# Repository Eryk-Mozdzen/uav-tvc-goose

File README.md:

# Thrust Vector Control Single Rotor UAV ''Goose''

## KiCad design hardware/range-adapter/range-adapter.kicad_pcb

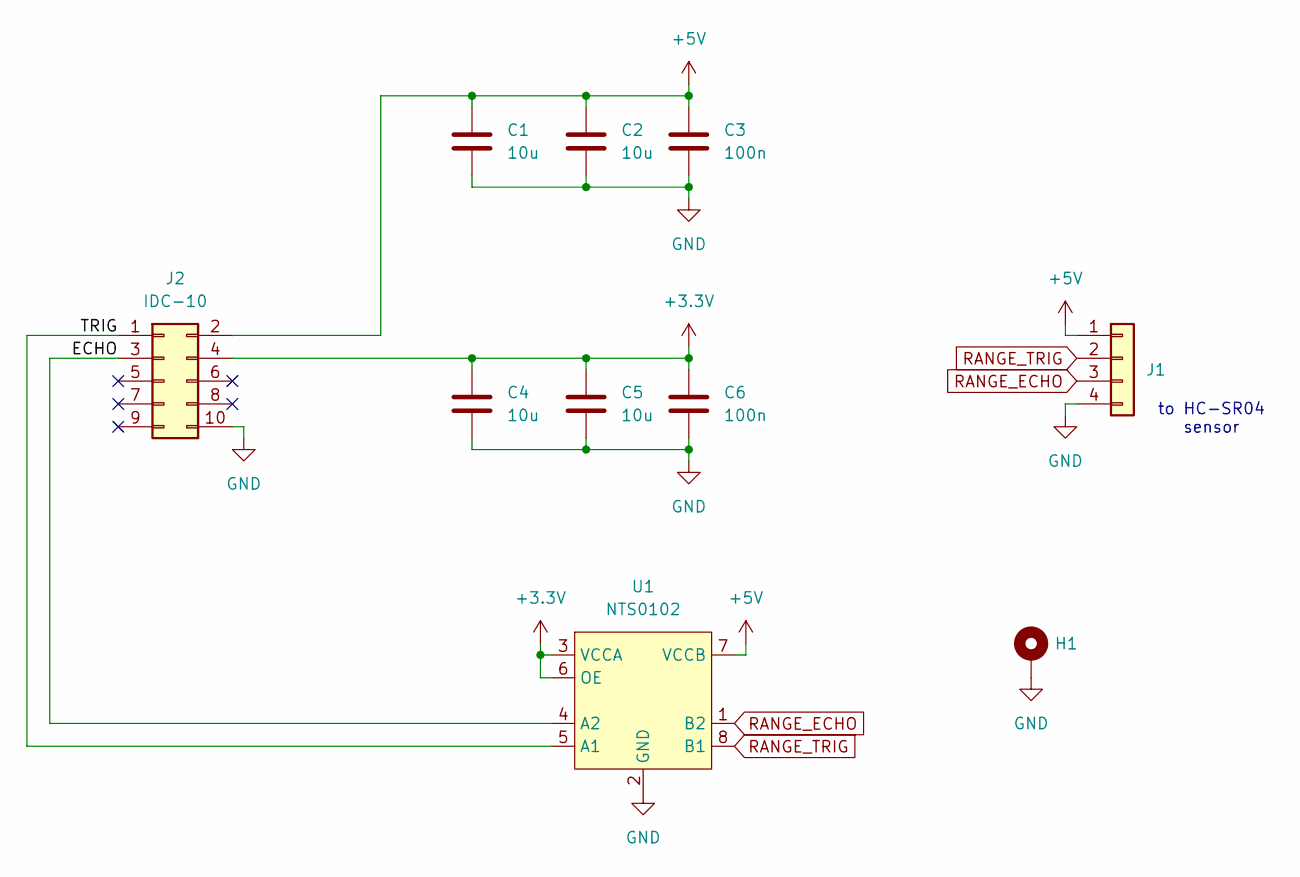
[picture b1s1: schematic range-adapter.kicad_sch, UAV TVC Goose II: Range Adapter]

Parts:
C1, C2, C4, C5: 10u; C_0603_1608Metric
C3, C6: 100n; C_0603_1608Metric
H1: MountingHole_Pad; MountingHole_3.5mm_Pad_Via
J1: Conn_01x04; header_1x4_not_used
J2: IDC-10; IDC-10-vertical
U1: NTS0102

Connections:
+3.3V: C4.1, C5.1, C6.1, J2.4, U1.3 (VCCA), U1.6 (OE)
+5V: C1.1, C2.1, C3.1, J1.1, J2.2, U1.7 (VCCB)
/ECHO: J2.3, U1.4 (A2)
/TRIG: J2.1, U1.5 (A1)
GND: C1.2, C2.2, C3.2, C4.2, C5.2, C6.2, H1.1, J1.4, J2.10, U1.2 (GND)
RANGE_ECHO: J1.3, U1.1 (B2)
RANGE_TRIG: J1.2, U1.8 (B1)

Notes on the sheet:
to HC-SR04 sensor

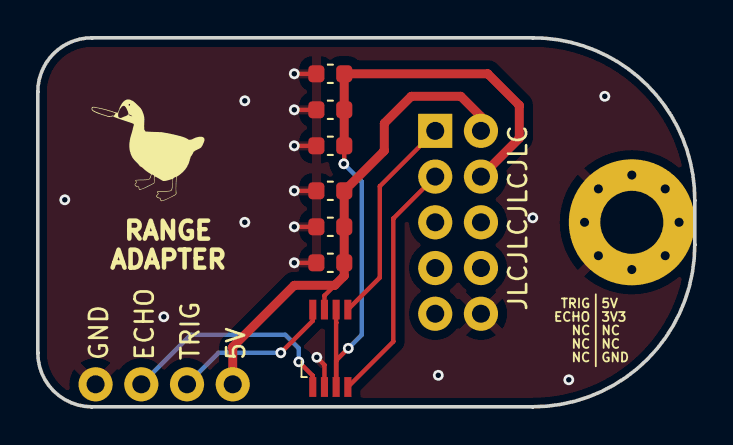
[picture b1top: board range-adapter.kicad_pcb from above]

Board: 2 copper layers, 36.5 x 20.5 mm, 10 parts (0 on the bottom side), 7 nets.

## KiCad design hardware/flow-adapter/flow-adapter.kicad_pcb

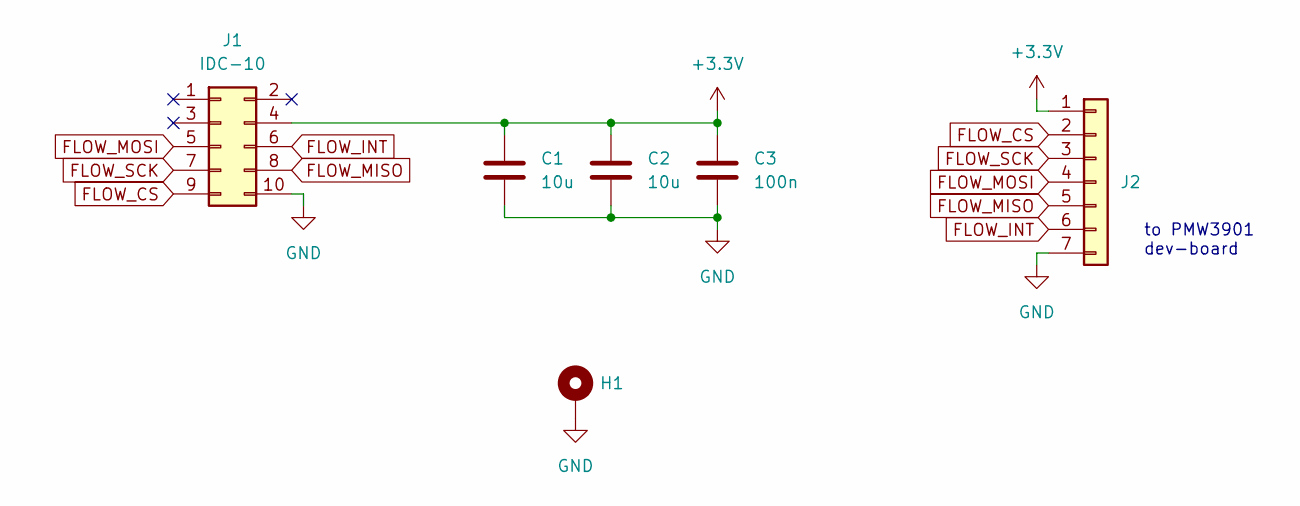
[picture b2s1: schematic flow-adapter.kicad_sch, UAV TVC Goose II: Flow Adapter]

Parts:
C1, C2: 10u; C_0603_1608Metric
C3: 100n; C_0603_1608Metric
H1: MountingHole_Pad; MountingHole_3.5mm_Pad_Via
J1: IDC-10; IDC-10-vertical
J2: Conn_01x07; header_1x7_not_used

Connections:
+3.3V: C1.1, C2.1, C3.1, J1.4, J2.1
FLOW_CS: J1.9, J2.2
FLOW_INT: J1.6, J2.6
FLOW_MISO: J1.8, J2.5
FLOW_MOSI: J1.5, J2.4
FLOW_SCK: J1.7, J2.3
GND: C1.2, C2.2, C3.2, H1.1, J1.10, J2.7

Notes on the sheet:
to PMW3901 dev-board

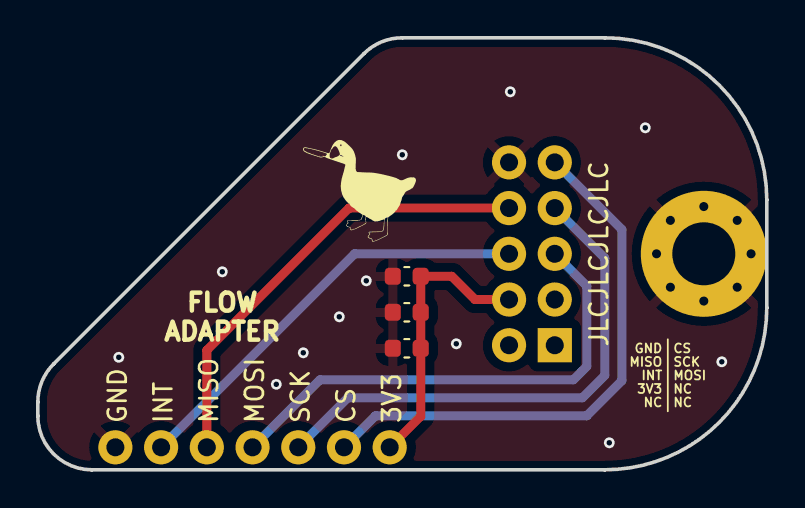
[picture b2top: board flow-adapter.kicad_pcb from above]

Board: 2 copper layers, 40.5 x 24.0 mm, 6 parts (0 on the bottom side), 7 nets.

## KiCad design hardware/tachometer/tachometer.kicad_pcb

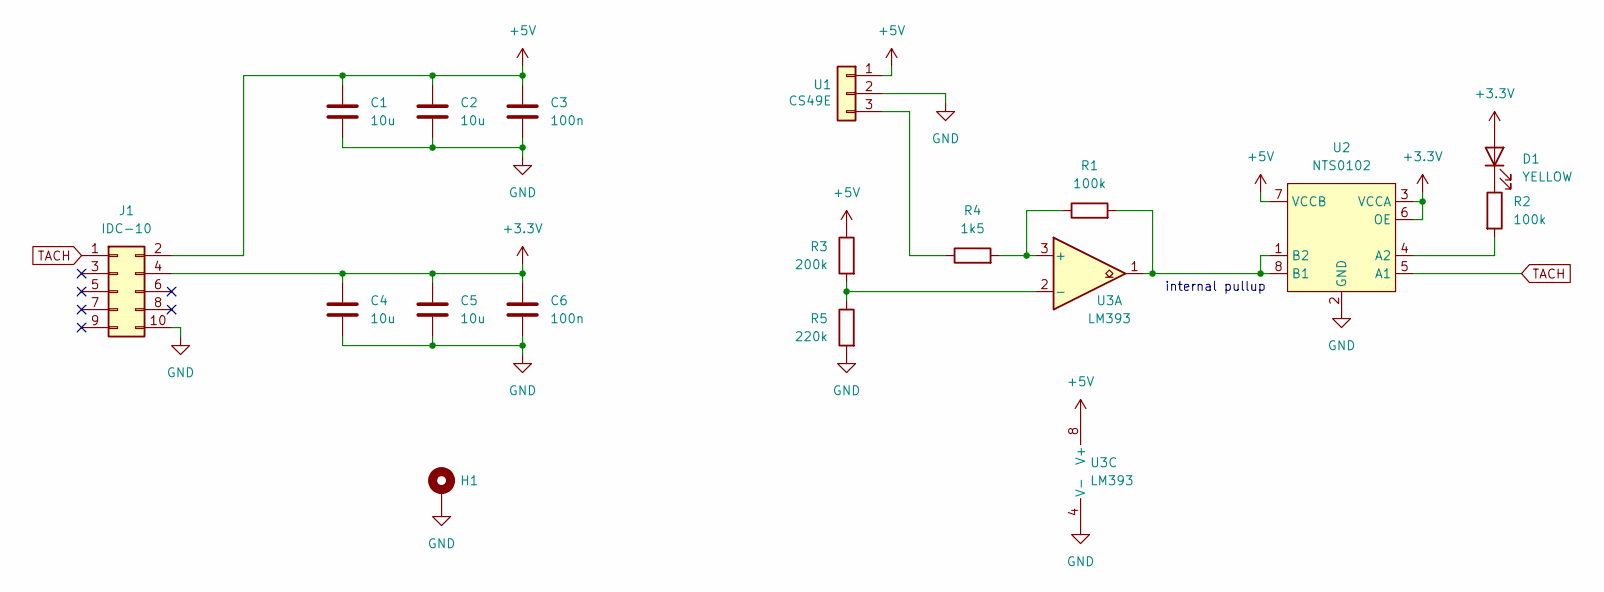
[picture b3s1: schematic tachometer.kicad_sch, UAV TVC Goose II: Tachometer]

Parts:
C1, C2, C4, C5: 10u; C_0603_1608Metric
C3, C6: 100n; C_0603_1608Metric
D1: YELLOW; LED_0603_1608Metric
H1: MountingHole_Pad; MountingHole_3.5mm_Pad_Via
J1: IDC-10; IDC-10-vertical
R1: 100k; R_0805_2012Metric
R2: 100k; R_0603_1608Metric
R3: 200k; R_0805_2012Metric
R4: 1k5; R_0805_2012Metric
R5: 220k; R_0805_2012Metric
U1: CS49E; hall
U2: NTS0102
U3: LM393

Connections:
+3.3V: C4.1, C5.1, C6.1, D1.2 (A), J1.4, U2.3 (VCCA), U2.6 (OE)
+5V: C1.1, C2.1, C3.1, J1.2, R3.1, U1.1, U2.7 (VCCB), U3.8 (V+)
GND: C1.2, C2.2, C3.2, C4.2, C5.2, C6.2, H1.1, J1.10, R5.2, U1.2, U2.2 (GND), U3.4 (V-)
unnamed: D1.1 (K), R2.1
unnamed: R4.1, U1.3
unnamed: R2.2, U2.4 (A2)
unnamed: R1.2, U2.1 (B2), U2.8 (B1), U3.1
unnamed: R1.1, R4.2, U3.3 (+)
unnamed: R3.2, R5.1, U3.2 (-)
TACH: J1.1, U2.5 (A1)

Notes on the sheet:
internal pullup

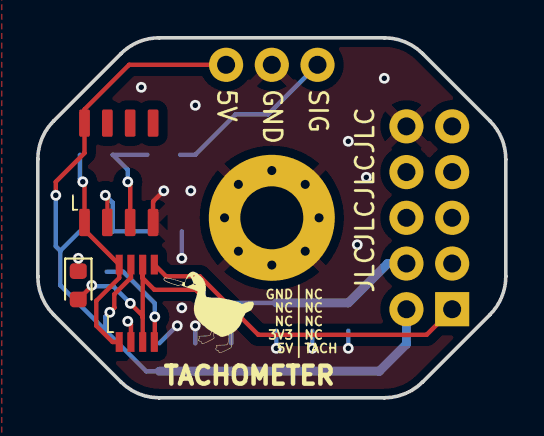
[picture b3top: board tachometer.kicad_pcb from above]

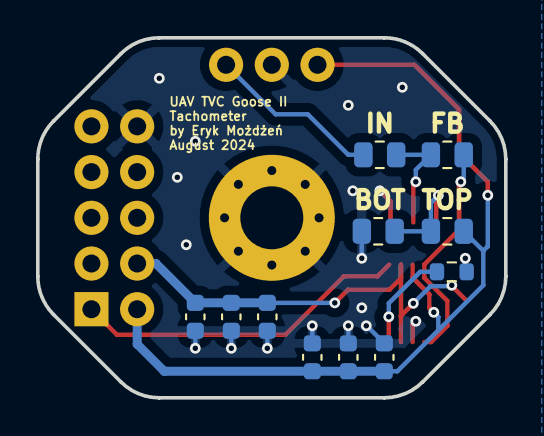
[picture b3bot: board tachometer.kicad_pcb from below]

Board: 2 copper layers, 26.0 x 20.0 mm, 17 parts (12 on the bottom side), 10 nets.

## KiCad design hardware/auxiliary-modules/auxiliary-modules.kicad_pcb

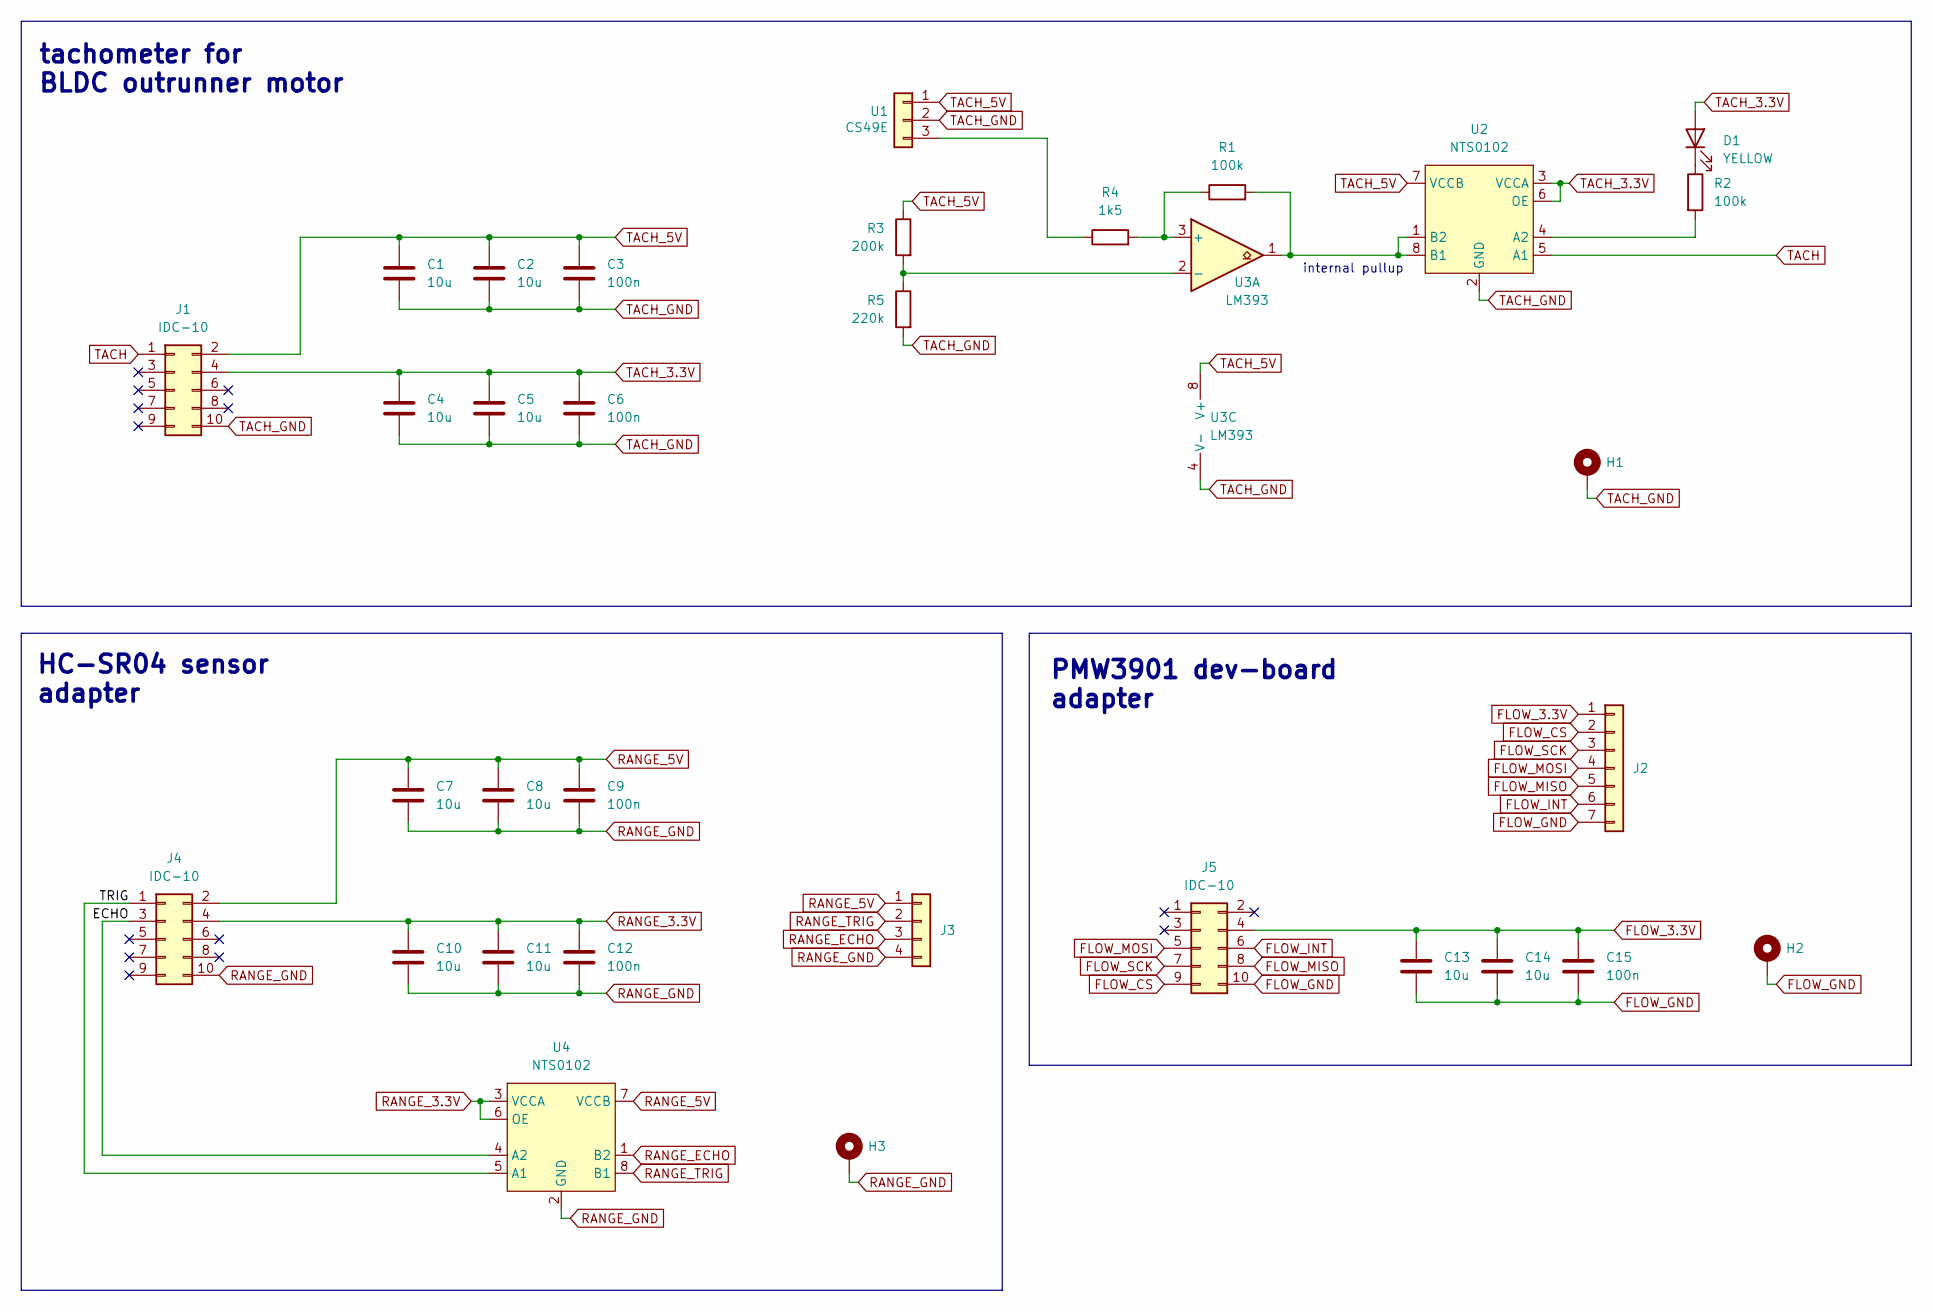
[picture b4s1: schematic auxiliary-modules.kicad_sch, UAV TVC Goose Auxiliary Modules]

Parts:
C1, C2, C4, C5, C7, C8, C10, C11, C13, C14: 10u; C_0603_1608Metric
C3, C6, C9, C12, C15: 100n; C_0603_1608Metric
D1: YELLOW; LED_0603_1608Metric
H1, H2, H3: MountingHole_Pad; MountingHole_3.5mm_Pad_Via
J1, J4, J5: IDC-10; IDC-10_vertical
J2: Conn_01x07; header_1x7
J3: Conn_01x04; header_1x4
R1: 100k; R_0805_2012Metric
R2: 100k; R_0603_1608Metric
R3: 200k; R_0805_2012Metric
R4: 1k5; R_0805_2012Metric
R5: 220k; R_0805_2012Metric
U1: CS49E; hall
U2, U4: NTS0102
U3: LM393

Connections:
/ECHO: J4.3, U4.4 (A2)
/TRIG: J4.1, U4.5 (A1)
FLOW_3.3V: C13.1, C14.1, C15.1, J2.1, J5.4
FLOW_CS: J2.2, J5.9
FLOW_GND: C13.2, C14.2, C15.2, H2.1, J2.7, J5.10
FLOW_INT: J2.6, J5.6
FLOW_MISO: J2.5, J5.8
FLOW_MOSI: J2.4, J5.5
FLOW_SCK: J2.3, J5.7
unnamed: D1.1 (K), R2.1
unnamed: R4.1, U1.3
unnamed: R2.2, U2.4 (A2)
unnamed: R1.2, U2.1 (B2), U2.8 (B1), U3.1
unnamed: R1.1, R4.2, U3.3 (+)
unnamed: R3.2, R5.1, U3.2 (-)
RANGE_3.3V: C10.1, C11.1, C12.1, J4.4, U4.3 (VCCA), U4.6 (OE)
RANGE_5V: C7.1, C8.1, C9.1, J3.1, J4.2, U4.7 (VCCB)
RANGE_ECHO: J3.3, U4.1 (B2)
RANGE_GND: C7.2, C8.2, C9.2, C10.2, C11.2, C12.2, H3.1, J3.4, J4.10, U4.2 (GND)
RANGE_TRIG: J3.2, U4.8 (B1)
TACH: J1.1, U2.5 (A1)
TACH_3.3V: C4.1, C5.1, C6.1, D1.2 (A), J1.4, U2.3 (VCCA), U2.6 (OE)
TACH_5V: C1.1, C2.1, C3.1, J1.2, R3.1, U1.1, U2.7 (VCCB), U3.8 (V+)
TACH_GND: C1.2, C2.2, C3.2, C4.2, C5.2, C6.2, H1.1, J1.10, R5.2, U1.2, U2.2 (GND), U3.4 (V-)

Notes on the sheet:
internal pullup
HC-SR04 sensor adapter
tachometer for BLDC outrunner motor
PMW3901 dev-board adapter

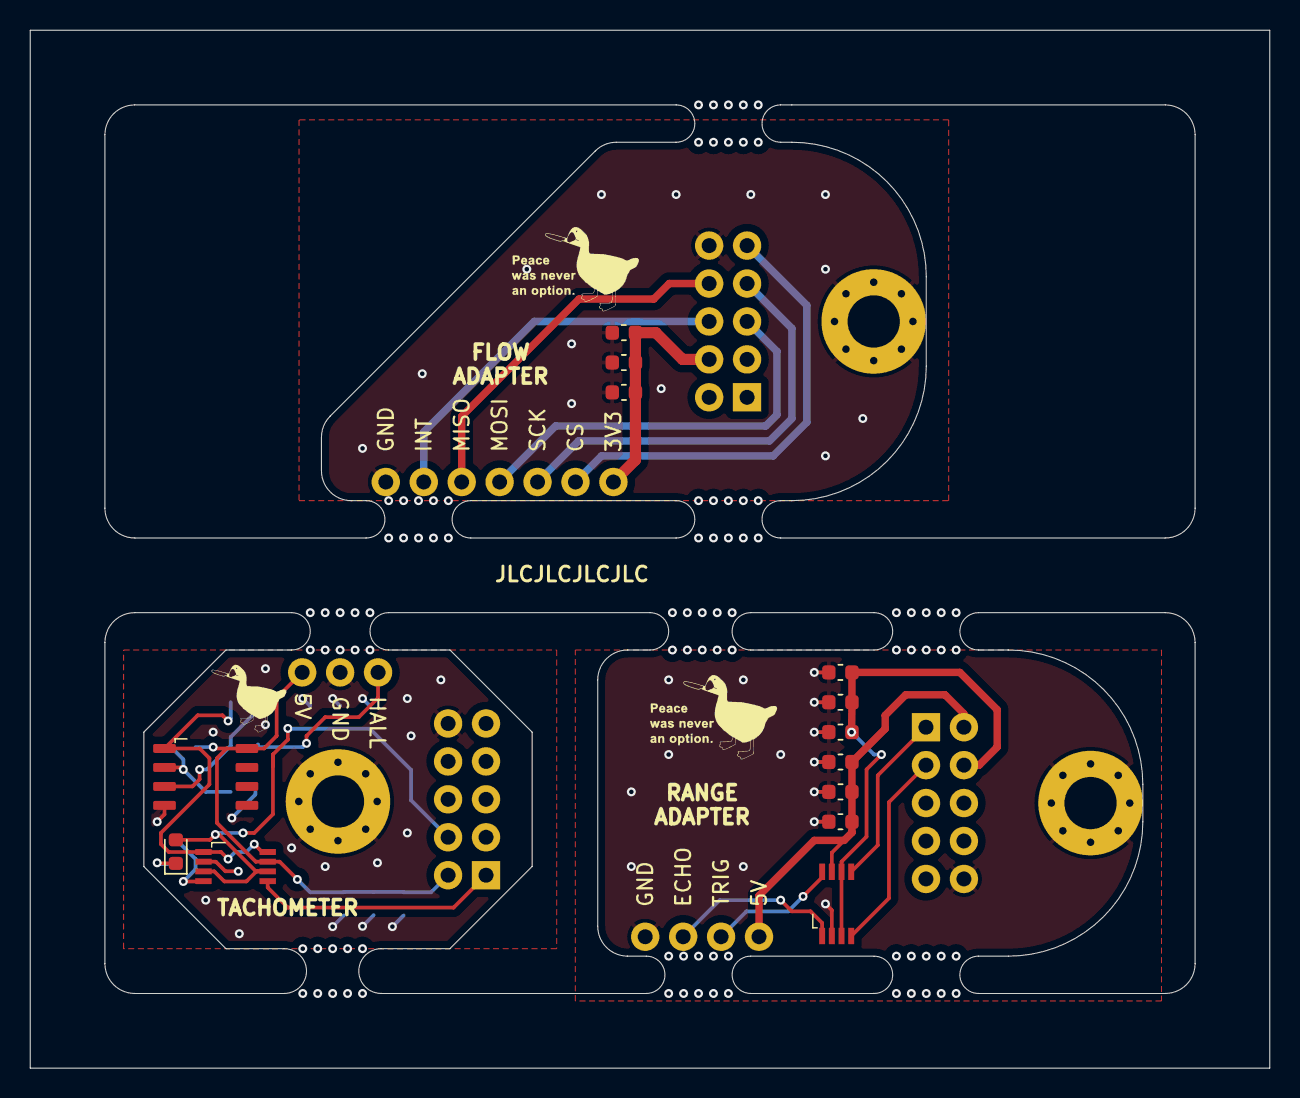
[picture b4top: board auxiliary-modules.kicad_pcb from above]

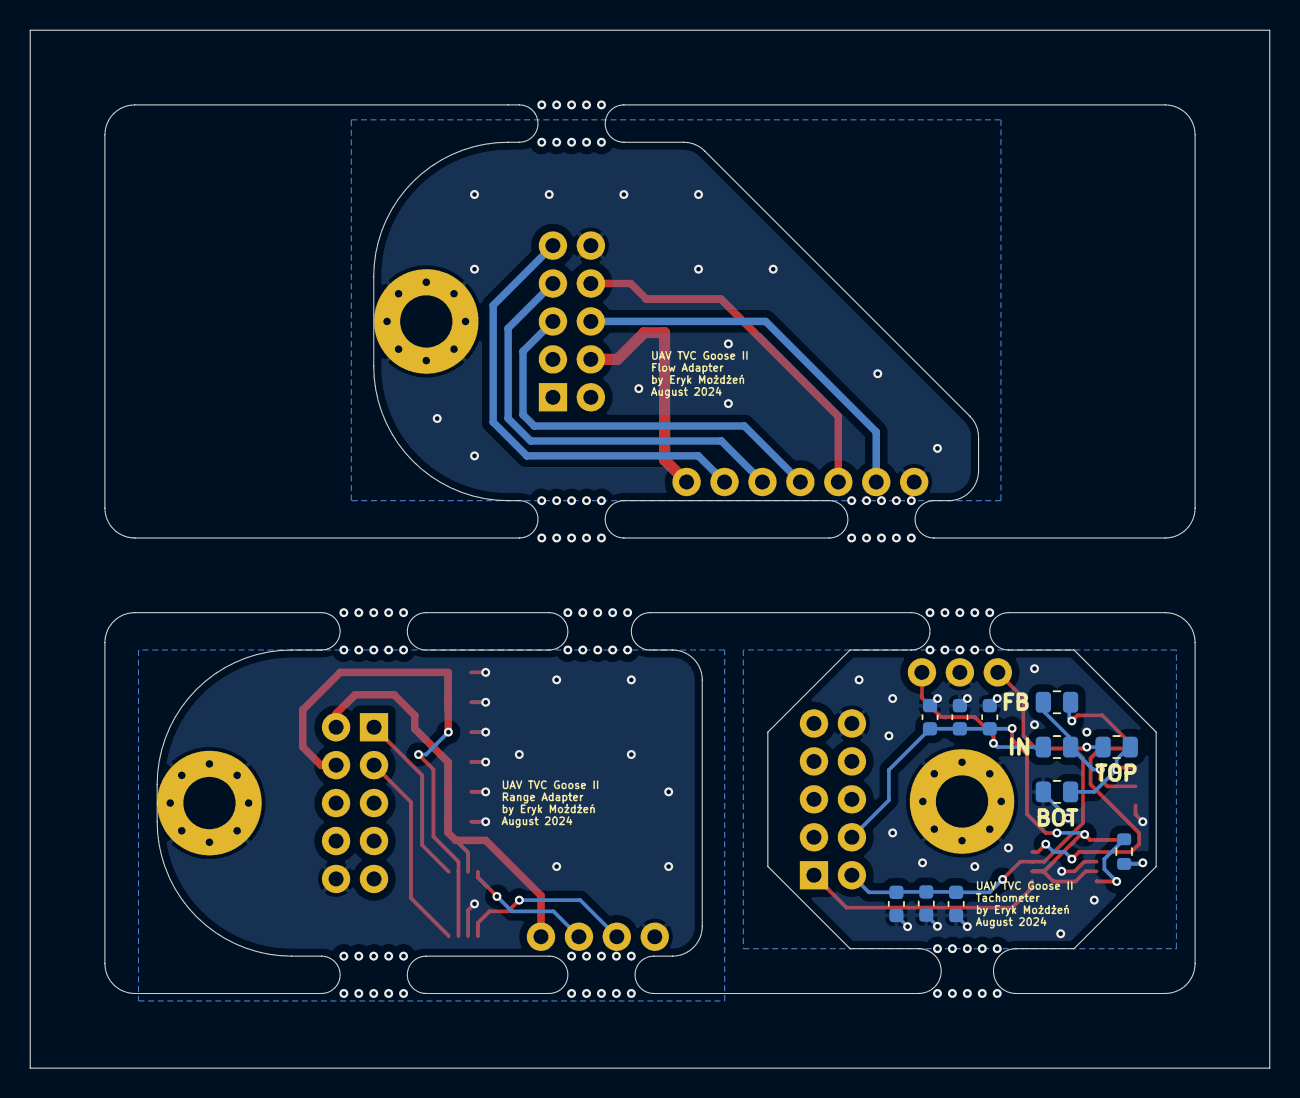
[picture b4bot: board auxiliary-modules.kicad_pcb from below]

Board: 2 copper layers, 83.0 x 69.5 mm, 33 parts (12 on the bottom side), 24 nets.

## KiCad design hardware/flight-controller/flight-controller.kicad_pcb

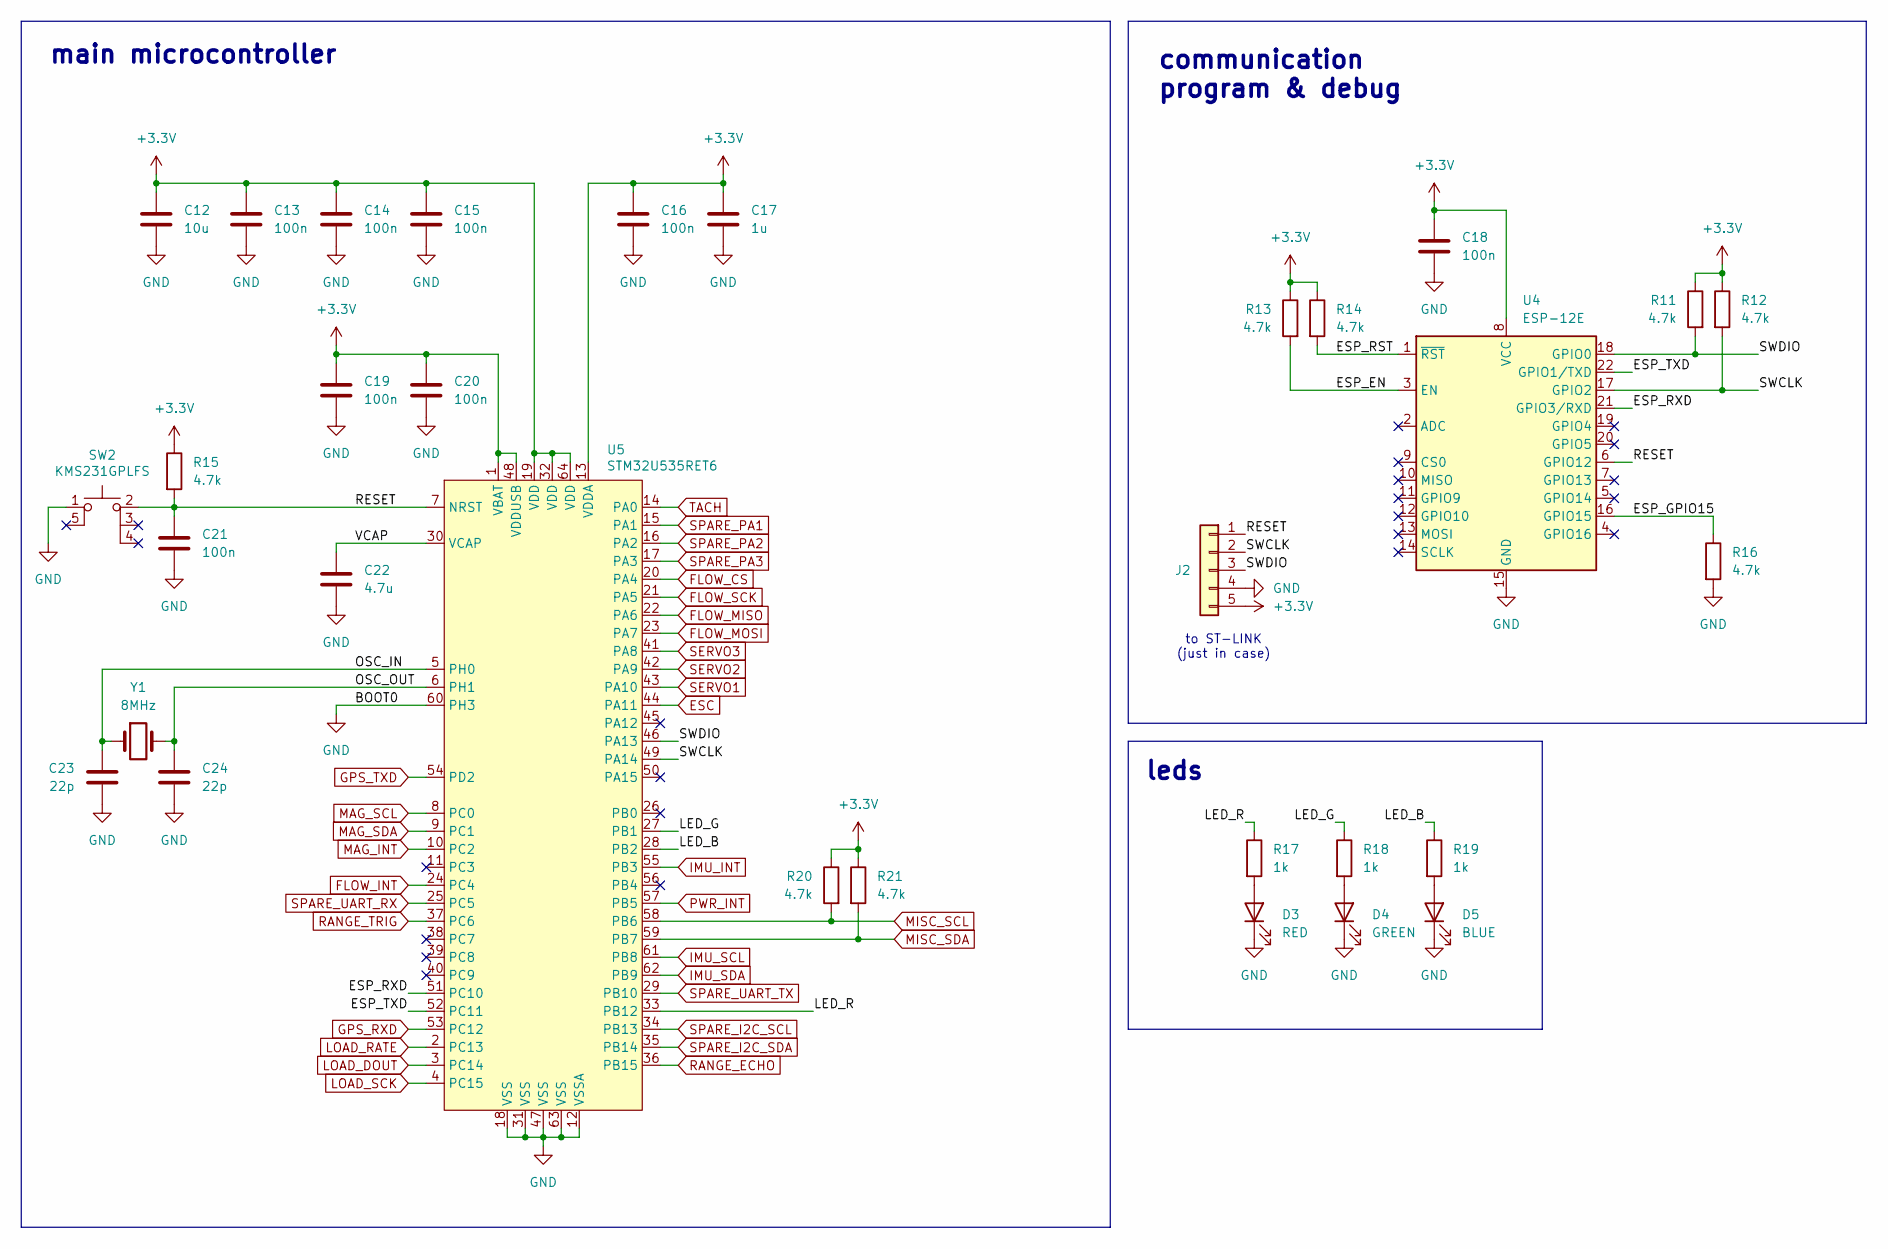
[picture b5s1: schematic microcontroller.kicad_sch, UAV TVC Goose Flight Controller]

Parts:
C12: 10u; C_0603_1608Metric
C13, C14, C15, C16, C18, C19, C20, C21: 100n; C_0603_1608Metric
C17: 1u; C_0603_1608Metric
C22: 4.7u; C_0603_1608Metric
C23, C24: 22p; C_0603_1608Metric
D3: RED; LED_0603_1608Metric
D4: GREEN; LED_0603_1608Metric
D5: BLUE; LED_0603_1608Metric
J2: Conn_01x05; header_1x5_not_used
R11, R12, R13, R14, R15, R16, R20, R21: 4.7k; R_0603_1608Metric
R17, R18, R19: 1k; R_0603_1608Metric
SW2: KMS231GPLFS
U4: ESP-12E
U5: STM32U535RET6
Y1: 8MHz; oscillator_5032_2

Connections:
+3.3V: C12.1, C13.1, C14.1, C15.1, C16.1, C17.1, C18.1, C19.1, C20.1, J2.5, R11.1, R12.1, R13.1, R14.1, R15.1, R20.1, R21.1, U4.8 (VCC), U5.1 (VBAT), U5.13 (VDDA), U5.19 (VDD), U5.32 (VDD), U5.48 (VDDUSB), U5.64 (VDD); also elsewhere on the board
/microcontroller/ESP_EN: R13.2, U4.3 (EN)
/microcontroller/ESP_GPIO15: R16.1, U4.16 (GPIO15)
/microcontroller/ESP_RST: R14.2, U4.1 (~RST)
/microcontroller/ESP_RXD: U4.21 (GPIO3/RXD), U5.51 (PC10)
/microcontroller/ESP_TXD: U4.22 (GPIO1/TXD), U5.52 (PC11)
/microcontroller/LED_B: R19.1, U5.28 (PB2)
/microcontroller/LED_G: R18.1, U5.27 (PB1)
/microcontroller/LED_R: R17.1, U5.33 (PB12)
/microcontroller/OSC_IN: C23.1, U5.5 (PH0), Y1.1
/microcontroller/OSC_OUT: C24.1, U5.6 (PH1), Y1.2
/microcontroller/RESET: C21.1, J2.1, R15.2, SW2.2, U4.6 (GPIO12), U5.7 (NRST)
/microcontroller/SWCLK: J2.2, R12.2, U4.17 (GPIO2), U5.49 (PA14)
/microcontroller/SWDIO: J2.3, R11.2, U4.18 (GPIO0), U5.46 (PA13)
/microcontroller/VCAP: C22.1, U5.30 (VCAP)
ESC: U5.44 (PA11); also elsewhere on the board
FLOW_CS: U5.20 (PA4); also elsewhere on the board
FLOW_INT: U5.24 (PC4); also elsewhere on the board
FLOW_MISO: U5.22 (PA6); also elsewhere on the board
FLOW_MOSI: U5.23 (PA7); also elsewhere on the board
FLOW_SCK: U5.21 (PA5); also elsewhere on the board
GND: C12.2, C13.2, C14.2, C15.2, C16.2, C17.2, C18.2, C19.2, C20.2, C21.2, C22.2, C23.2, C24.2, D3.1 (K), D4.1 (K), D5.1 (K), J2.4, R16.2, SW2.1, U4.15 (GND), U5.12 (VSSA), U5.18 (VSS), U5.31 (VSS), U5.47 (VSS), U5.60 (PH3), U5.63 (VSS); also elsewhere on the board
GPS_RXD: U5.53 (PC12); also elsewhere on the board
GPS_TXD: U5.54 (PD2); also elsewhere on the board
IMU_INT: U5.55 (PB3); also elsewhere on the board
IMU_SCL: U5.61 (PB8); also elsewhere on the board
IMU_SDA: U5.62 (PB9); also elsewhere on the board
LOAD_DOUT: U5.3 (PC14); also elsewhere on the board
LOAD_RATE: U5.2 (PC13); also elsewhere on the board
LOAD_SCK: U5.4 (PC15); also elsewhere on the board
MAG_INT: U5.10 (PC2); also elsewhere on the board
MAG_SCL: U5.8 (PC0); also elsewhere on the board
MAG_SDA: U5.9 (PC1); also elsewhere on the board
MISC_SCL: R20.2, U5.58 (PB6); also elsewhere on the board
MISC_SDA: R21.2, U5.59 (PB7); also elsewhere on the board
unnamed: D3.2 (A), R17.2
unnamed: D4.2 (A), R18.2
unnamed: D5.2 (A), R19.2
PWR_INT: U5.57 (PB5); also elsewhere on the board
RANGE_ECHO: U5.36 (PB15); also elsewhere on the board
RANGE_TRIG: U5.37 (PC6); also elsewhere on the board
SERVO1: U5.43 (PA10); also elsewhere on the board
SERVO2: U5.42 (PA9); also elsewhere on the board
SERVO3: U5.41 (PA8); also elsewhere on the board
SPARE_I2C_SCL: U5.34 (PB13); also elsewhere on the board
SPARE_I2C_SDA: U5.35 (PB14); also elsewhere on the board
SPARE_PA1: U5.15 (PA1); also elsewhere on the board
SPARE_PA2: U5.16 (PA2); also elsewhere on the board
SPARE_PA3: U5.17 (PA3); also elsewhere on the board
SPARE_UART_RX: U5.25 (PC5); also elsewhere on the board
SPARE_UART_TX: U5.29 (PB10); also elsewhere on the board
TACH: U5.14 (PA0); also elsewhere on the board

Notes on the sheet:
main microcontroller
to ST-LINK (just in case)
communication program & debug
leds

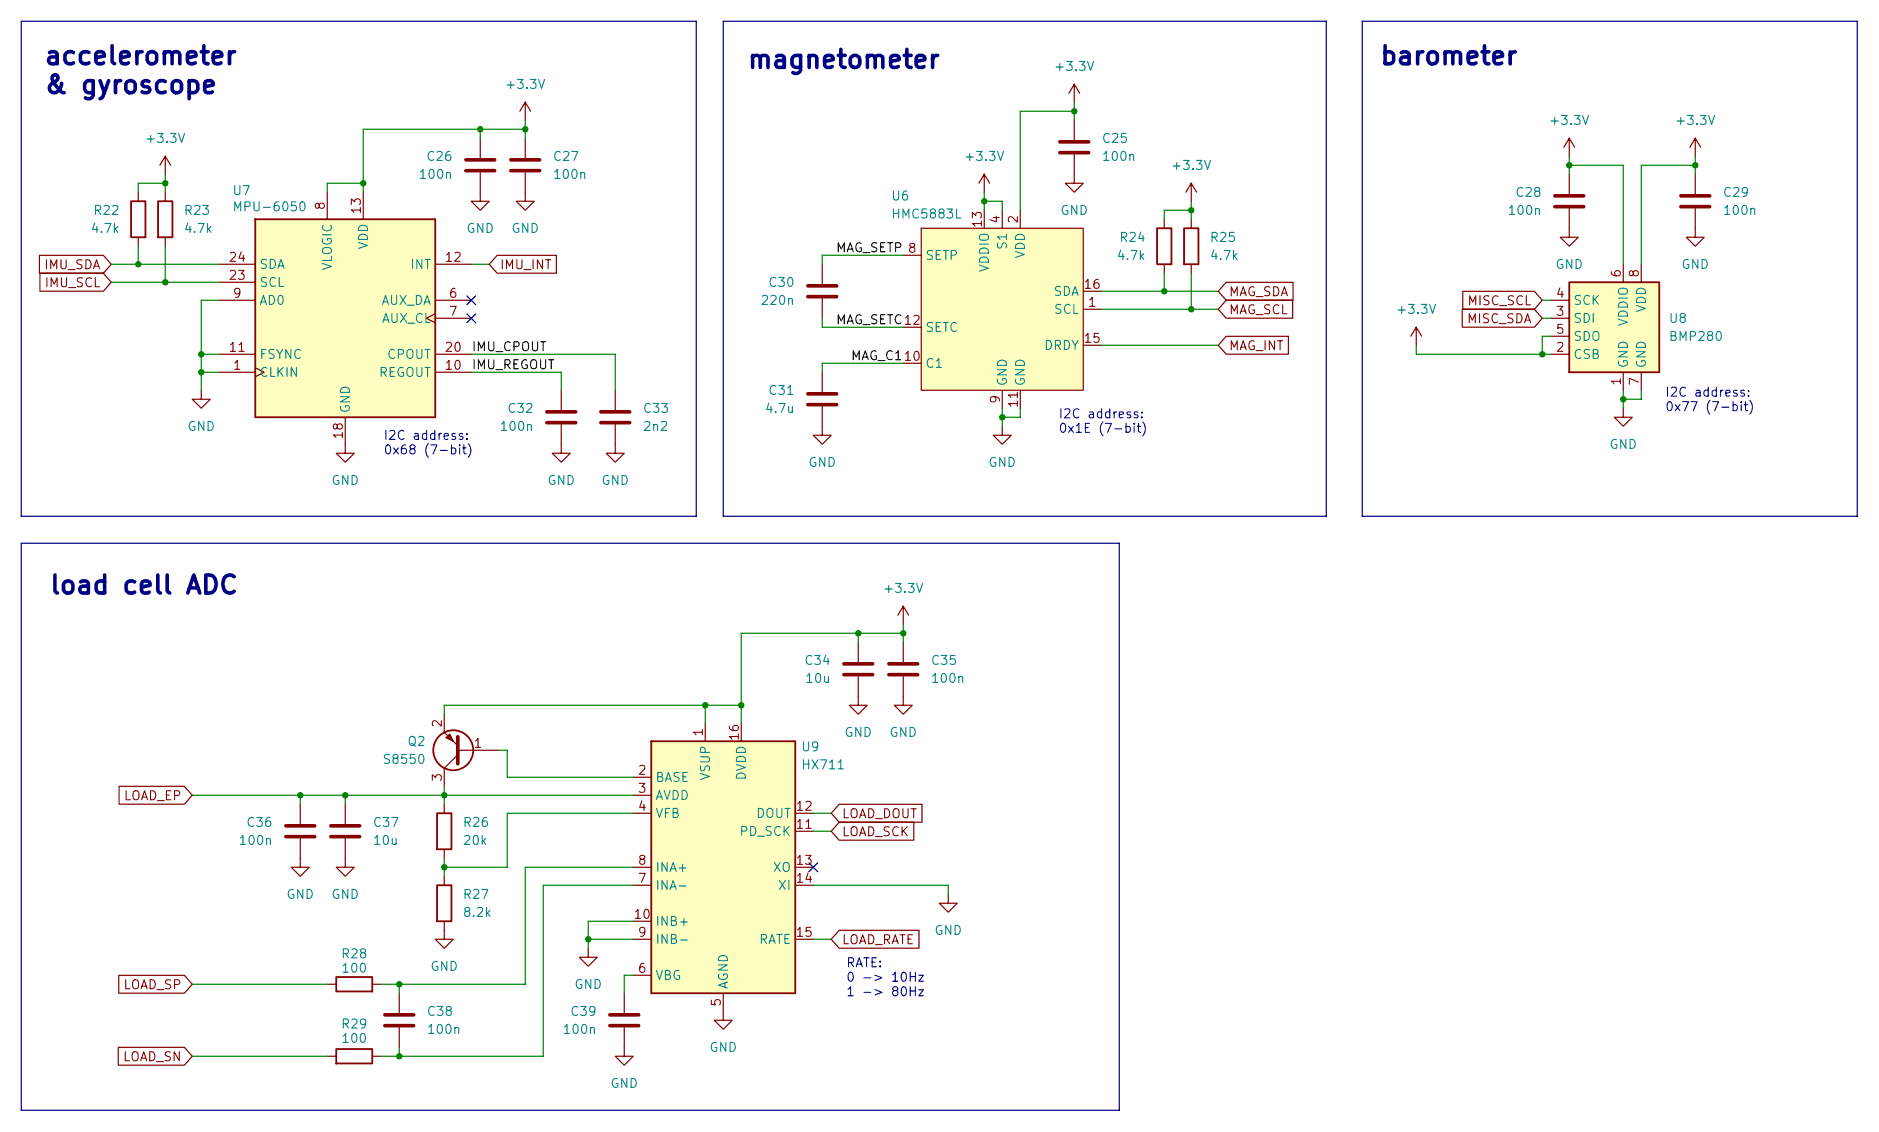
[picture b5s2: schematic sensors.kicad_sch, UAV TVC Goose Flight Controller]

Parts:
C25, C26, C27, C28, C29, C32, C35, C36, C38, C39: 100n; C_0603_1608Metric
C30: 220n; C_0603_1608Metric
C31: 4.7u; C_0603_1608Metric
C33: 2n2; C_0603_1608Metric
C34, C37: 10u; C_0603_1608Metric
Q2: S8550; SOT-23
R22, R23, R24, R25: 4.7k; R_0603_1608Metric
R26: 20k; R_0603_1608Metric
R27: 8.2k; R_0603_1608Metric
R28, R29: 100; R_0603_1608Metric
U6: HMC5883L; HMC5883L_handsolder
U7: MPU-6050; MPU6050_handsolder
U8: BMP280; BMP280_handsolder
U9: HX711

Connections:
+3.3V: C25.1, C26.1, C27.1, C28.1, C29.1, C34.1, C35.1, Q2.2 (E), R22.1, R23.1, R24.1, R25.1, U6.2 (VDD), U6.4 (S1), U6.13 (VDDIO), U7.8 (VLOGIC), U7.13 (VDD), U8.2 (CSB), U8.5 (SDO), U8.6 (VDDIO), U8.8 (VDD), U9.1 (VSUP), U9.16 (DVDD); also elsewhere on the board
/sensors/IMU_CPOUT: C33.1, U7.20 (CPOUT)
/sensors/IMU_REGOUT: C32.1, U7.10 (REGOUT)
/sensors/MAG_C1: C31.1, U6.10 (C1)
/sensors/MAG_SETC: C30.2, U6.12 (SETC)
/sensors/MAG_SETP: C30.1, U6.8 (SETP)
GND: C25.2, C26.2, C27.2, C28.2, C29.2, C31.2, C32.2, C33.2, C34.2, C35.2, C36.2, C37.2, C39.2, R27.2, U6.9 (GND), U6.11 (GND), U7.1 (CLKIN), U7.9 (AD0), U7.11 (FSYNC), U7.18 (GND), U8.1 (GND), U8.7 (GND), U9.5 (AGND), U9.9 (INB-), U9.10 (INB+), U9.14 (XI); also elsewhere on the board
IMU_INT: U7.12 (INT); also elsewhere on the board
IMU_SCL: R23.2, U7.23 (SCL); also elsewhere on the board
IMU_SDA: R22.2, U7.24 (SDA); also elsewhere on the board
LOAD_DOUT: U9.12 (DOUT); also elsewhere on the board
LOAD_EP: C36.1, C37.1, Q2.3 (C), R26.1, U9.3 (AVDD); also elsewhere on the board
LOAD_RATE: U9.15 (RATE); also elsewhere on the board
LOAD_SCK: U9.11 (PD_SCK); also elsewhere on the board
LOAD_SN: R29.2; also elsewhere on the board
LOAD_SP: R28.1; also elsewhere on the board
MAG_INT: U6.15 (DRDY); also elsewhere on the board
MAG_SCL: R25.2, U6.1 (SCL); also elsewhere on the board
MAG_SDA: R24.2, U6.16 (SDA); also elsewhere on the board
MISC_SCL: U8.4 (SCK); also elsewhere on the board
MISC_SDA: U8.3 (SDI); also elsewhere on the board
unnamed: Q2.1 (B), U9.2 (BASE)
unnamed: C38.1, R28.2, U9.8 (INA+)
unnamed: C38.2, R29.1, U9.7 (INA-)
unnamed: C39.1, U9.6 (VBG)
unnamed: R26.2, R27.1, U9.4 (VFB)

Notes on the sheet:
barometer
accelerometer & gyroscope
I2C address: 0x77 (7-bit)
RATE: 0 -> 10Hz 1 -> 80Hz
load cell ADC
I2C address: 0x68 (7-bit)
I2C address: 0x1E (7-bit)
magnetometer
